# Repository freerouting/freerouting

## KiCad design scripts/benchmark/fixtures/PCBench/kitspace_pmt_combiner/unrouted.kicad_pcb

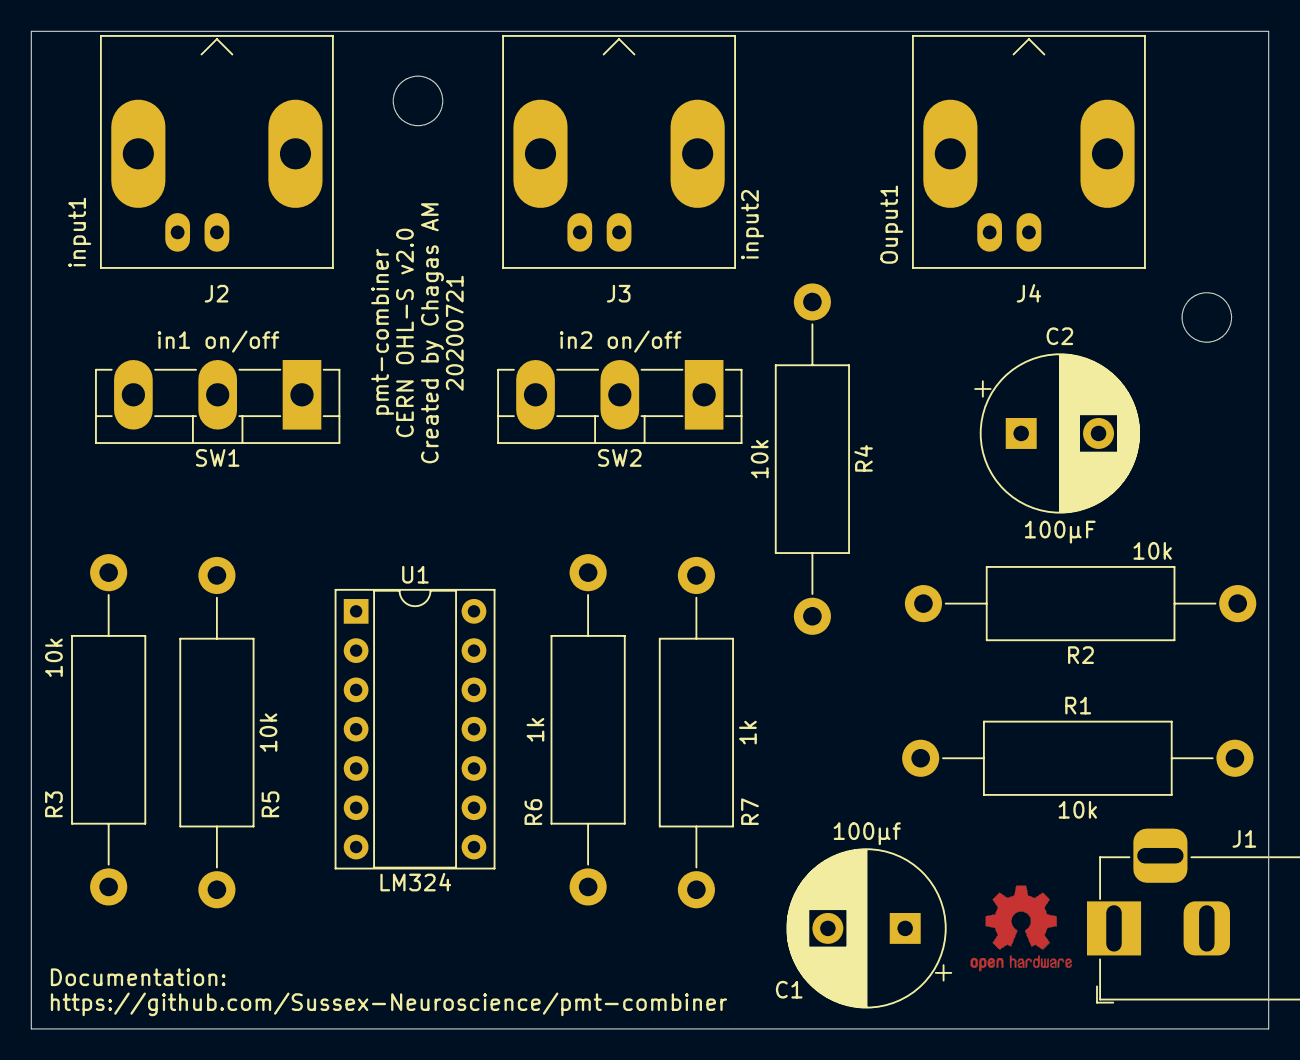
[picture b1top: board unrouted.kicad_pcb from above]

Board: 2 copper layers, 80.0 x 64.5 mm, 16 parts (0 on the bottom side), 11 nets, no tracks yet.

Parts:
C1: 100µf; CP_Radial_D10.0mm_P5.00mm
C2: 100µF; CP_Radial_D10.0mm_P5.00mm
J1: Barrel_Jack_MountingPin; BarrelJack_Horizontal
J2: input1; BNC_Amphenol_B6252HB-NPP3G-50_Horizontal
J3: input2; BNC_Amphenol_B6252HB-NPP3G-50_Horizontal
J4: Ouput1; BNC_Amphenol_B6252HB-NPP3G-50_Horizontal
R1, R2, R3, R4, R5: 10k; R_Axial_DIN0414_L11.9mm_D4.5mm_P20.32mm_Horizontal
R6, R7: 1k; R_Axial_DIN0414_L11.9mm_D4.5mm_P20.32mm_Horizontal
SW1: in1 on/off; TO-3P-3_Vertical
SW2: in2 on/off; TO-3P-3_Vertical
U1: LM324; DIP-14_W7.62mm_Socket

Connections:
GND: C1.2, C2.1, J2.2, J3.2, J4.2, R1.1, R2.2, SW1.3, SW2.3, U1.3, U1.5
unnamed: C1.1, J1.2, R1.2, U1.11
unnamed: C2.2, J1.1, R2.1, U1.4
unnamed: J2.1, SW1.1
unnamed: J3.1, SW2.1
unnamed: J4.1, R7.2, U1.7
unnamed: R3.1, SW1.2
unnamed: R3.2, R4.2, R5.1, U1.2
unnamed: R4.1, SW2.2
unnamed: R5.2, R6.1, U1.1
unnamed: R6.2, R7.1, U1.6

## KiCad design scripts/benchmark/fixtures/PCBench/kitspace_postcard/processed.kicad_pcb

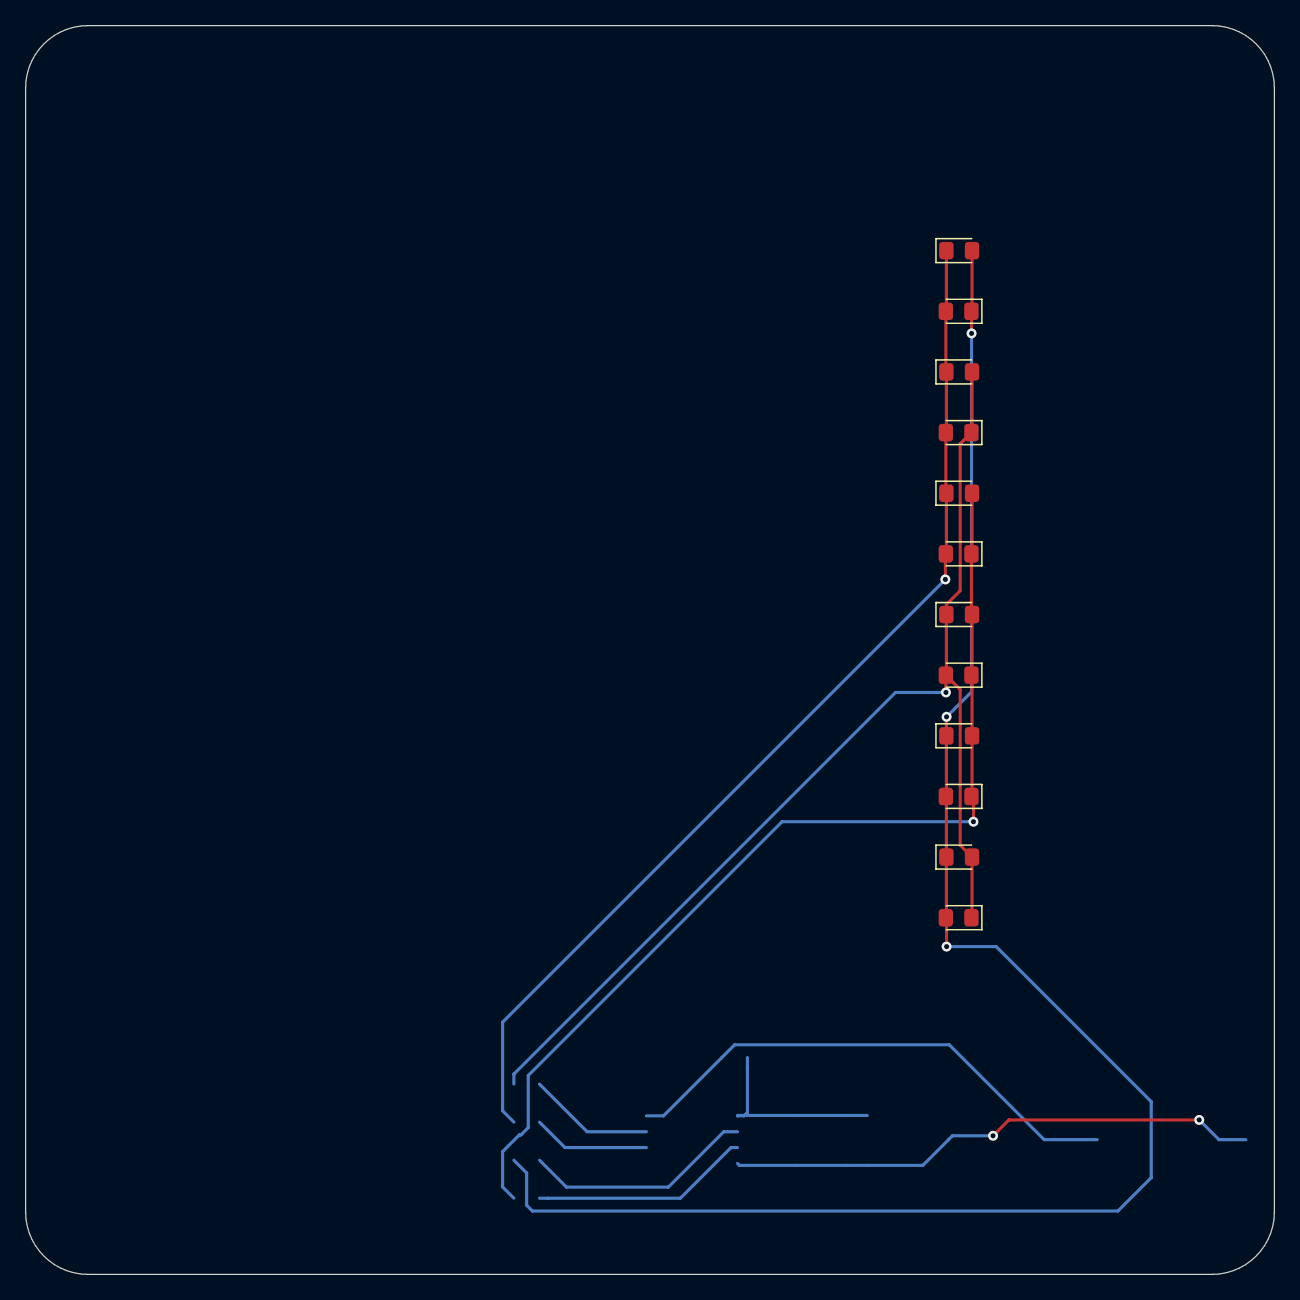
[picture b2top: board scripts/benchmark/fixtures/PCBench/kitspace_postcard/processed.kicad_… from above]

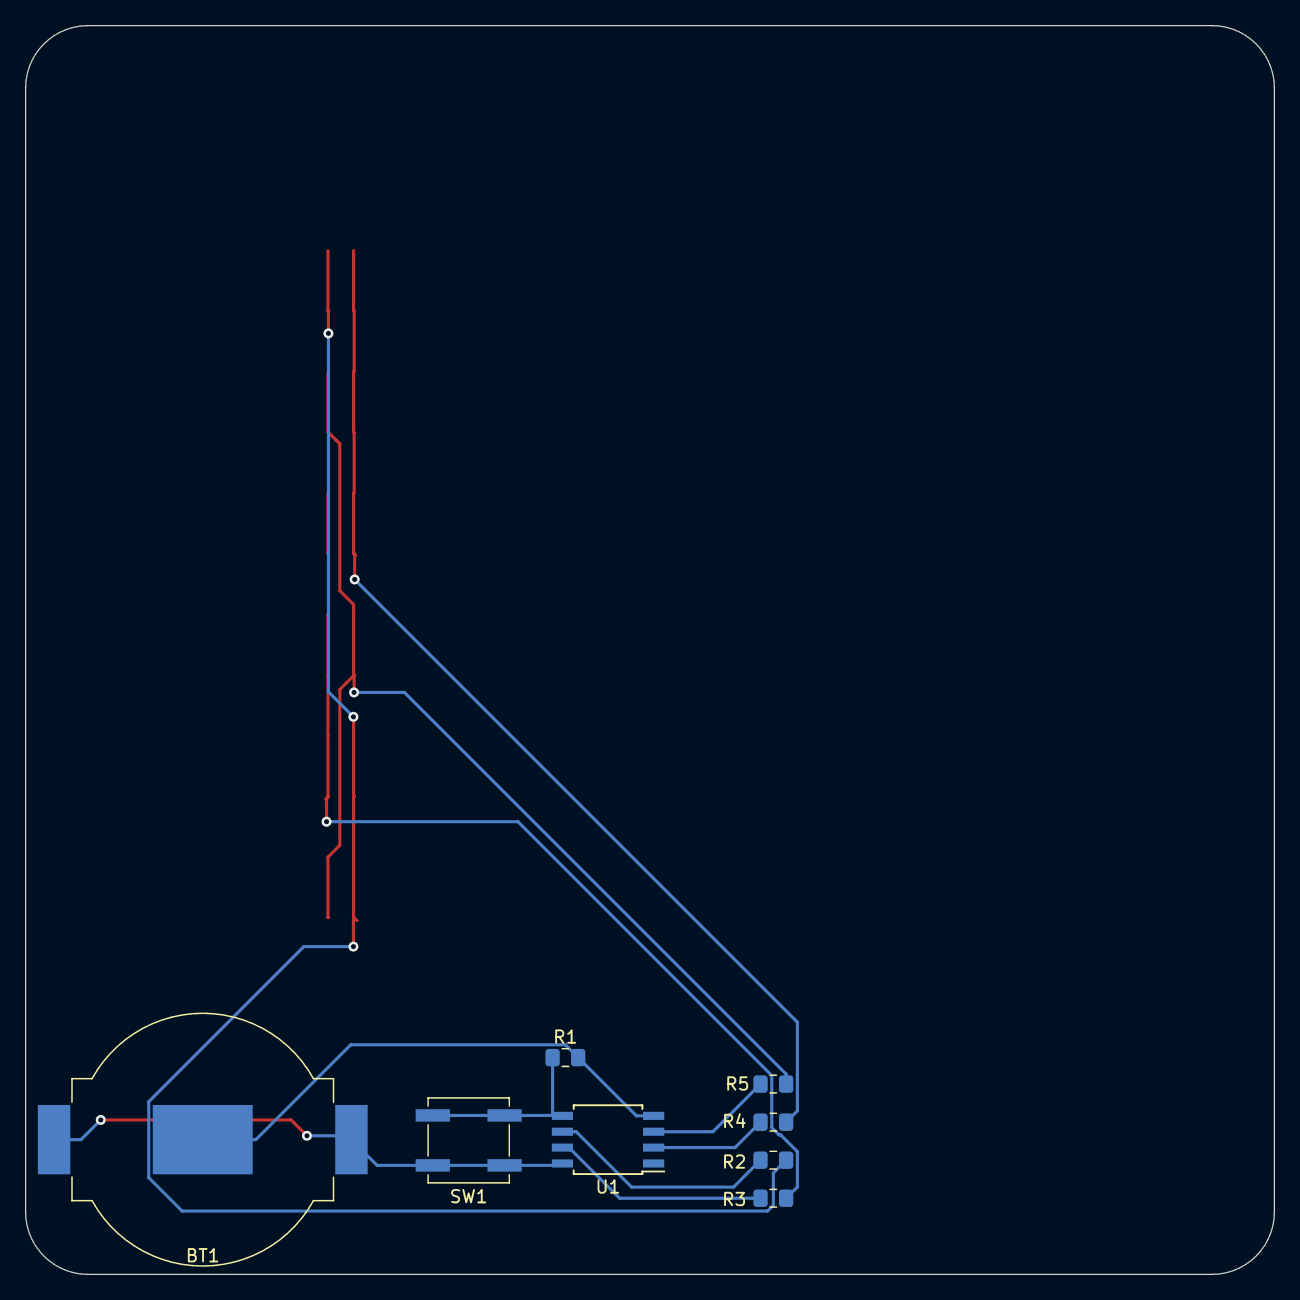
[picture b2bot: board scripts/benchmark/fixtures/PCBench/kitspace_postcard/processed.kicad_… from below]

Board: 2 copper layers, 100.0 x 100.0 mm, 20 parts (8 on the bottom side), 11 nets.

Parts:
BT1: Battery; BatteryHolder_MPD_BC2003_1x2032
D1, D2, D3, D4, D5, D6, D7, D8, D9, D10, D11, D12: LED; LED_0805_2012Metric_Pad1.15x1.40mm_HandSolder
R1, R2, R3, R4, R5: R; R_0805_2012Metric_Pad1.15x1.40mm_HandSolder
SW1: SW_Push; SW_SPST_B3SL-1002P
U1: ATtiny85-20SU; SOIJ-8_5.3x5.3mm_P1.27mm

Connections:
Earth: BT1.2, R1.2, U1.4
unnamed: D1.1, D2.2, D4.2, D5.1, D11.2, D12.1, R3.1
unnamed: D1.2, D4.1, D7.2, D8.1, D9.2, D10.1, R2.1
unnamed: D2.1, D3.2, D5.2, D6.1, D7.1, D8.2, R4.1
unnamed: D3.1, D6.2, D9.1, D10.2, D11.1, D12.2, R5.1
unnamed: R1.1, SW1.2, U1.5
unnamed: R2.2, U1.6
unnamed: R3.2, U1.7
unnamed: R4.2, U1.2
unnamed: R5.2, U1.3
VDD: BT1.1, SW1.1, U1.8

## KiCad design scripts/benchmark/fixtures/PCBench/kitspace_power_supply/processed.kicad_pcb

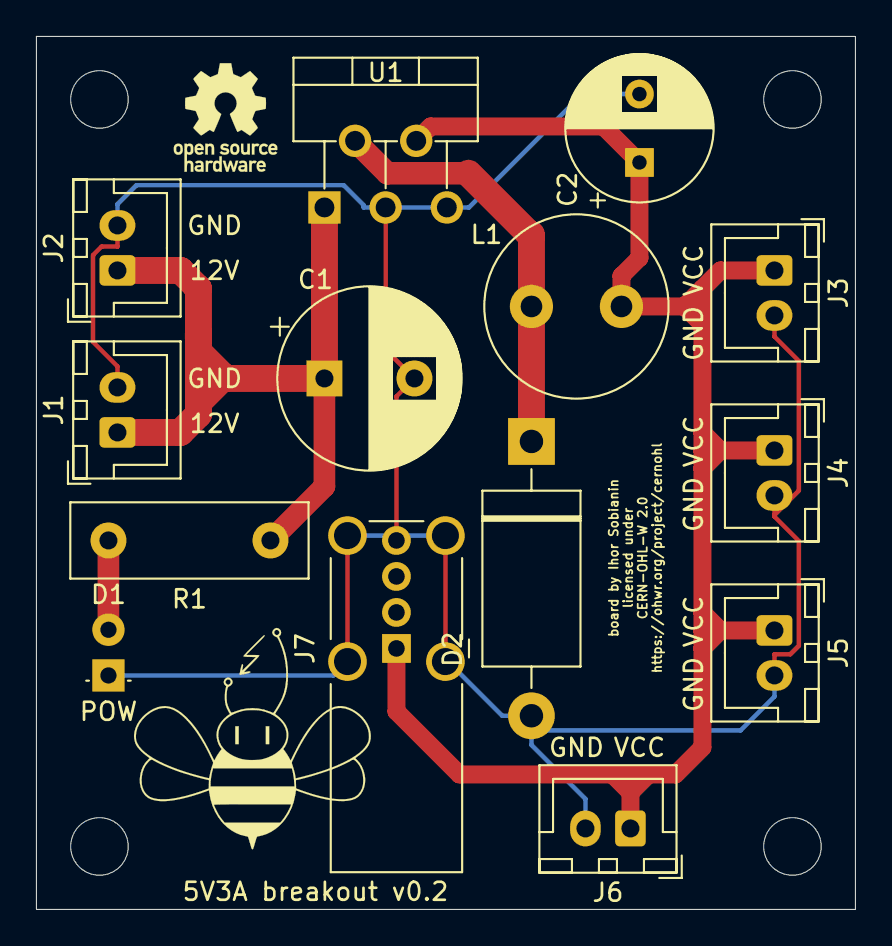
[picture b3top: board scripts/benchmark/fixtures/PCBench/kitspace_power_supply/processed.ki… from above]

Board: 2 copper layers, 45.5 x 48.5 mm, 19 parts (0 on the bottom side), 5 nets.

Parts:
C1: 680µ; CP_Radial_D10.0mm_P5.00mm
C2: 220µ; CP_Radial_D8.0mm_P3.80mm
D1: LED; LED_D3.0mm
D2: D_Schottky; D_DO-201_P15.24mm_Horizontal
J1, J2, J3, J4, J5, J6: Conn_01x02; JST_XH_B2B-XH-A_1x02_P2.50mm_Vertical
J7: USB_A; USB_A_Wuerth_614004134726_Horizontal
L1: 33µH; L_Radial_D10.0mm_P5.00mm_Neosid_SD12_style3
R1: 560; R_Box_L13.0mm_W4.0mm_P9.00mm
REF1, REF2, REF3, REF4: MountingHole_3.2mm_M3_DIN965
REF5: OSHW-Logo_5.7x6mm_SilkScreen
U1: LM2596S-5; TO-220-5_P3.4x3.7mm_StaggerOdd_Lead3.8mm_Vertical

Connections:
GND: C1.2, C2.2, D1.1, D2.2, J1.2, J2.2, J3.2, J4.2, J5.2, J6.2, J7.4, J7.5, U1.3, U1.5
unnamed: C1.1, J1.1, J2.1, R1.1, U1.1
unnamed: C2.1, J3.1, J4.1, J5.1, J6.1, J7.1, L1.2, U1.4
unnamed: D1.2, R1.2
unnamed: D2.1, L1.1, U1.2

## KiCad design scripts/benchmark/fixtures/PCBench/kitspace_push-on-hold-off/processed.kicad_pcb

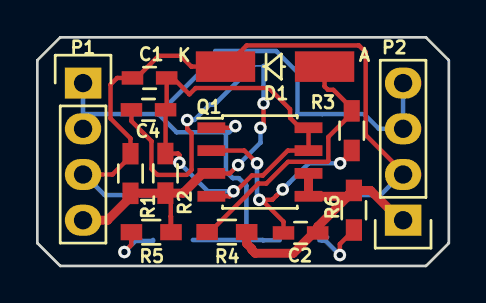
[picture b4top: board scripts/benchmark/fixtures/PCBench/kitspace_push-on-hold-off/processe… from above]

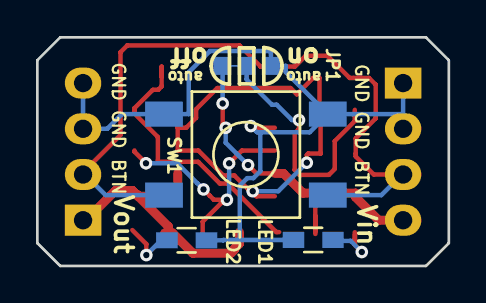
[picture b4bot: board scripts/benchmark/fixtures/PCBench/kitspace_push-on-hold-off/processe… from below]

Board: 2 copper layers, 22.9 x 12.7 mm, 17 parts (4 on the bottom side), 9 nets.

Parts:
C1: 1uF; C_0603_HandSoldering
C2: 10uF; C_0603_HandSoldering
C4: 0.1uF; C_0603_HandSoldering
D1: D; MiniMELF_Handsoldering
JP1: JUMPER3; SOLDER-JUMPER_2-WAY
LED1, LED2: LED; R_0603_HandSoldering
P1, P2: CONN_01X04; Pin_Header_Straight_1x04
Q1: IRF7309IPBF; SOIC-8_3.9x4.9mm_Pitch1.27mm
R1: 10k; R_0603_HandSoldering
R2, R4: 100k; R_0603_HandSoldering
R3: 300k; R_0603_HandSoldering
R5, R6: 1k; R_0603_HandSoldering
SW1: SW_PUSH_SMALL; FSM2JSMA

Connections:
/Button: C1.2, D1.1, P1.3, P2.2, R1.2, SW1.1
/Vin: C4.1, JP1.2, JP1.3, P1.4, Q1.3, R1.1, R2.1, R5.1
/Vout: C2.2, P2.1, Q1.5, Q1.6, R4.1, R6.1
GND: JP1.1, LED1.1, LED2.1, P1.1, P1.2, P2.3, P2.4, Q1.1, SW1.2
unnamed: C1.1, C4.2, Q1.4, Q1.7, Q1.8, R2.2
unnamed: C2.1, Q1.2, R3.2
unnamed: D1.2, R3.1, R4.2
unnamed: LED1.2, R5.2
unnamed: LED2.2, R6.2

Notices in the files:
scripts/benchmark/fixtures/PCBench/kitspace_pmt_combiner/unrouted.kicad_pcb:
CERN OHL-S v2.0
scripts/benchmark/fixtures/PCBench/kitspace_power_supply/processed.kicad_pcb:
licensed under
CERN-OHL-W 2.0
